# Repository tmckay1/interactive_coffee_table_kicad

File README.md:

# KiCad Schematic for IR Interactive Coffee Table
The following repository contains all the KiCad files that are used to create the circuit for the interactive coffee table

The circuit is made up of 2 sections, with each section made up of the same smaller circuit. The smaller circuit contains a shift register that pushes data to a darlington array. This part is used to control turning on the IR Emitters. The smaller circuit also contains a multiplexer that reduces the amount of photodiode lines. There are power in and out lines, and both the shift register and multiplexer parts are able to be daisy chained.

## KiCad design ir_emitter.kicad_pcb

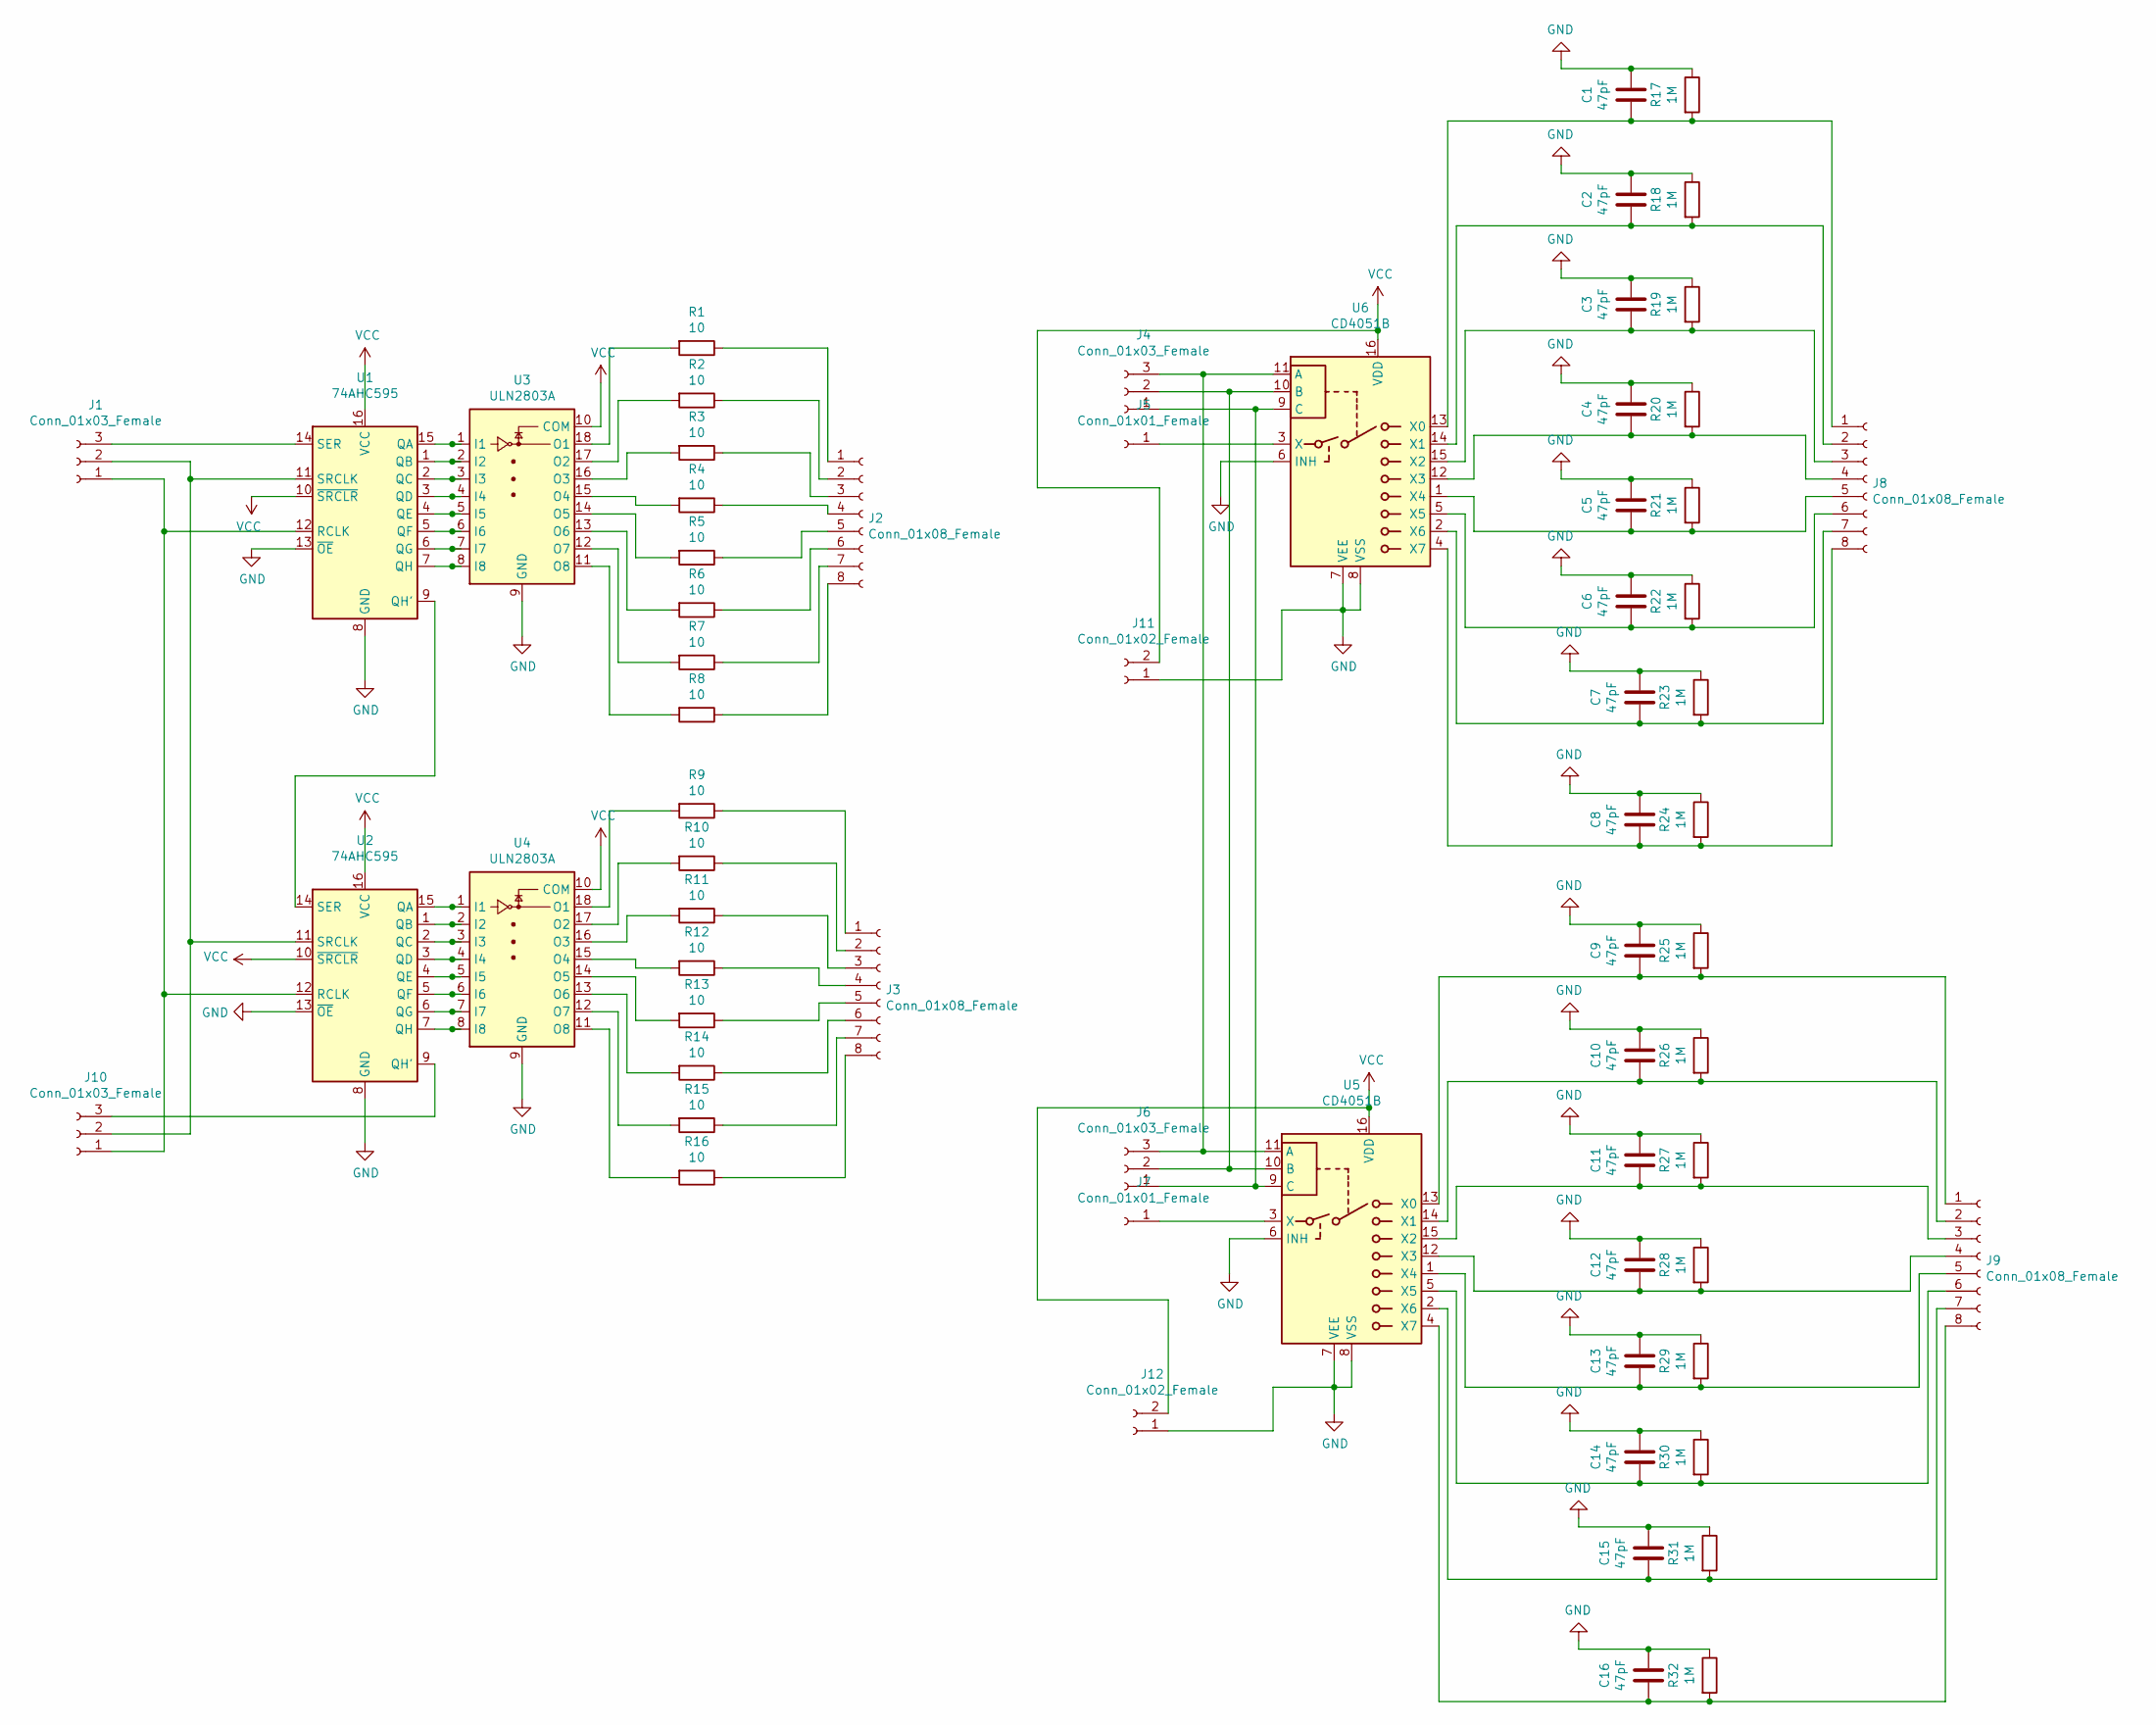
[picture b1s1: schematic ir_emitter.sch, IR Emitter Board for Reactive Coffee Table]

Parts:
C1, C2, C3, C4, C5, C6, C7, C8, C9, C10, C11, C12, C13, C14, C15, C16: 47pF; C_Disc_D7.5mm_W5.0mm_P7.50mm
J1, J4, J6, J10: Conn_01x03_Female; PinHeader_1x03_P2.54mm_Vertical
J2, J3, J8, J9: Conn_01x08_Female; PinHeader_1x08_P2.54mm_Vertical
J5, J7: Conn_01x01_Female; PinHeader_1x01_P2.54mm_Vertical
J11, J12: Conn_01x02_Female; PinHeader_1x02_P2.54mm_Vertical
R1, R2, R3, R4, R5, R6, R7, R8, R9, R10, R11, R12, R13, R14, R15, R16: 10; R_Axial_DIN0207_L6.3mm_D2.5mm_P7.62mm_Horizontal
R17, R18, R19, R20, R21, R22, R23, R24, R25, R26, R27, R28, R29, R30, R31, R32: 1M; R_Axial_DIN0309_L9.0mm_D3.2mm_P12.70mm_Horizontal
U1, U2: 74AHC595; DIP-16_W7.62mm_Socket
U3, U4: ULN2803A; DIP-18_W7.62mm_Socket
U5, U6: CD4051B; DIP-16_W7.62mm_Socket

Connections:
GND: C1.1, C2.1, C3.1, C4.1, C5.1, C6.1, C7.1, C8.1, C9.1, C10.1, C11.1, C12.1, C13.1, C14.1, C15.1, C16.1, J11.1, J12.1, R17.1, R18.1, R19.1, R20.1, R21.1, R22.1, R23.1, R24.1, R25.1, R26.1, R27.1, R28.1, R29.1, R30.1, R31.1, R32.1, U1.8 (GND), U1.13 (~OE), U2.8 (GND), U2.13 (~OE), U3.9 (GND), U4.9 (GND), U5.6 (INH), U5.7 (VEE), U5.8 (VSS), U6.6 (INH), U6.7 (VEE), U6.8 (VSS)
unnamed: C1.2, J8.1, R17.2, U6.13 (X0)
unnamed: C2.2, J8.2, R18.2, U6.14 (X1)
unnamed: C3.2, J8.3, R19.2, U6.15 (X2)
unnamed: C4.2, J8.4, R20.2, U6.12 (X3)
unnamed: C5.2, J8.5, R21.2, U6.1 (X4)
unnamed: C6.2, J8.6, R22.2, U6.5 (X5)
unnamed: C7.2, J8.7, R23.2, U6.2 (X6)
unnamed: C8.2, J8.8, R24.2, U6.4 (X7)
unnamed: C9.2, J9.1, R25.2, U5.13 (X0)
unnamed: C10.2, J9.2, R26.2, U5.14 (X1)
unnamed: C11.2, J9.3, R27.2, U5.15 (X2)
unnamed: C12.2, J9.4, R28.2, U5.12 (X3)
unnamed: C13.2, J9.5, R29.2, U5.1 (X4)
unnamed: C14.2, J9.6, R30.2, U5.5 (X5)
unnamed: C15.2, J9.7, R31.2, U5.2 (X6)
unnamed: C16.2, J9.8, R32.2, U5.4 (X7)
unnamed: J1.1, J10.1, U1.12 (RCLK), U2.12 (RCLK)
unnamed: J1.2, J10.2, U1.11 (SRCLK), U2.11 (SRCLK)
unnamed: J1.3, U1.14 (SER)
unnamed: J2.1, R1.1
unnamed: J2.2, R2.1
unnamed: J2.3, R3.1
unnamed: J2.4, R4.1
unnamed: J2.5, R5.1
unnamed: J2.6, R6.1
unnamed: J2.7, R7.1
unnamed: J2.8, R8.1
unnamed: J3.1, R9.1
unnamed: J3.2, R10.1
unnamed: J3.3, R11.1
unnamed: J3.4, R12.1
unnamed: J3.5, R13.1
unnamed: J3.6, R14.1
unnamed: J3.7, R15.1
unnamed: J3.8, R16.1
unnamed: J4.1, J6.1, U5.9 (C), U6.9 (C)
unnamed: J4.2, J6.2, U5.10 (B), U6.10 (B)
unnamed: J4.3, J6.3, U5.11 (A), U6.11 (A)
unnamed: J5.1, U6.3 (X)
unnamed: J7.1, U5.3 (X)
unnamed: J10.3, U2.9 (QH')
unnamed: R1.2, U3.18 (O1)
unnamed: R2.2, U3.17 (O2)
unnamed: R3.2, U3.16 (O3)
unnamed: R4.2, U3.15 (O4)
unnamed: R5.2, U3.14 (O5)
unnamed: R6.2, U3.13 (O6)
unnamed: R7.2, U3.12 (O7)
unnamed: R8.2, U3.11 (O8)
unnamed: R9.2, U4.18 (O1)
unnamed: R10.2, U4.17 (O2)
unnamed: R11.2, U4.16 (O3)
unnamed: R12.2, U4.15 (O4)
unnamed: R13.2, U4.14 (O5)
unnamed: R14.2, U4.13 (O6)
unnamed: R15.2, U4.12 (O7)
unnamed: R16.2, U4.11 (O8)
unnamed: U1.1 (QB), U3.2 (I2)
unnamed: U1.2 (QC), U3.3 (I3)
unnamed: U1.3 (QD), U3.4 (I4)
unnamed: U1.4 (QE), U3.5 (I5)
unnamed: U1.5 (QF), U3.6 (I6)
unnamed: U1.6 (QG), U3.7 (I7)
unnamed: U1.7 (QH), U3.8 (I8)
unnamed: U1.9 (QH'), U2.14 (SER)
unnamed: U1.15 (QA), U3.1 (I1)
unnamed: U2.1 (QB), U4.2 (I2)
unnamed: U2.2 (QC), U4.3 (I3)
unnamed: U2.3 (QD), U4.4 (I4)
unnamed: U2.4 (QE), U4.5 (I5)
unnamed: U2.5 (QF), U4.6 (I6)
unnamed: U2.6 (QG), U4.7 (I7)
unnamed: U2.7 (QH), U4.8 (I8)
unnamed: U2.15 (QA), U4.1 (I1)
VCC: J11.2, J12.2, U1.10 (~SRCLR), U1.16 (VCC), U2.10 (~SRCLR), U2.16 (VCC), U3.10 (COM), U4.10 (COM), U5.16 (VDD), U6.16 (VDD)

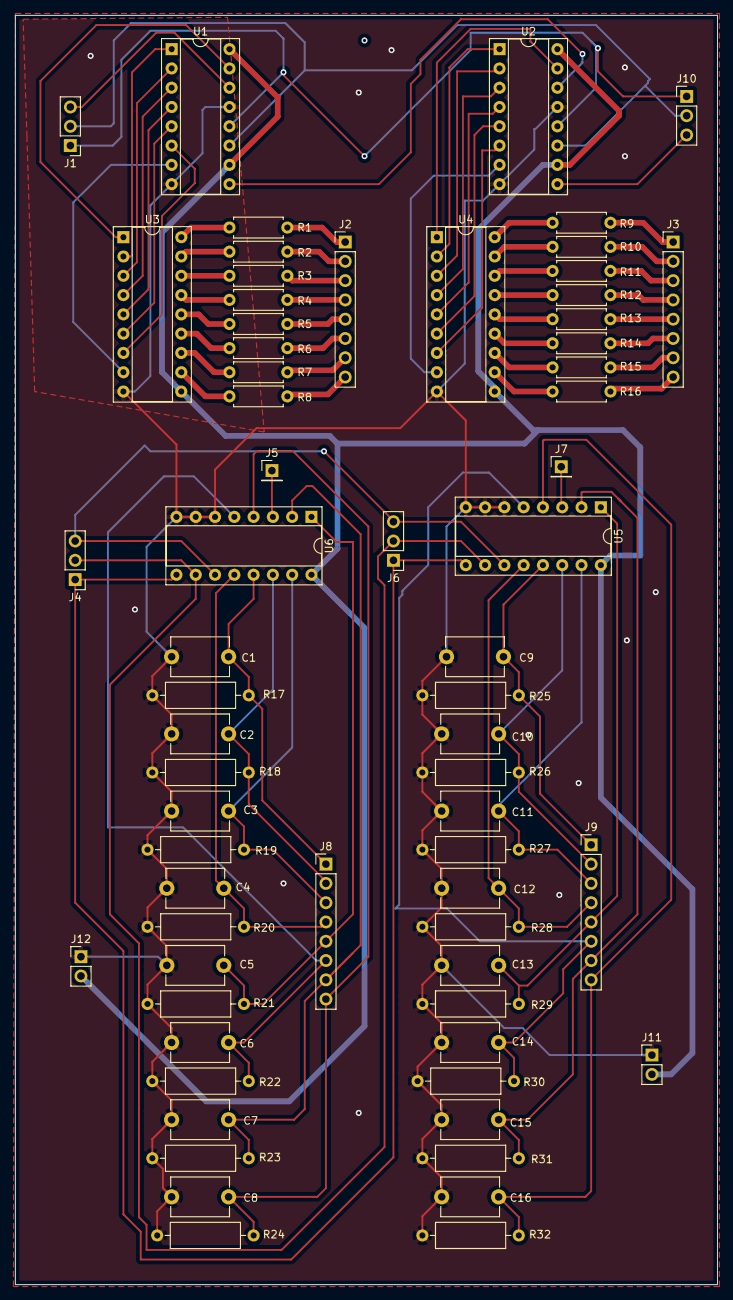
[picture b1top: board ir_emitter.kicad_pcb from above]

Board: 2 copper layers, 92.5 x 167.1 mm, 66 parts (0 on the bottom side), 76 nets.

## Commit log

2020-10-12 add version 2

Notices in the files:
ir_emitter.kicad_pcb:
License: CC BY 4.0
ir_emitter.sch:
https://creativecommons.org/licenses/by/4.0
